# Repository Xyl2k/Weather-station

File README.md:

Weather-station
===============

This is an Arduino powered weather station who run with 5V and who report datas on your own control panel.
You can also launch a cycle from the panel.
An Eagle typon is also available for those who want to print a PCB

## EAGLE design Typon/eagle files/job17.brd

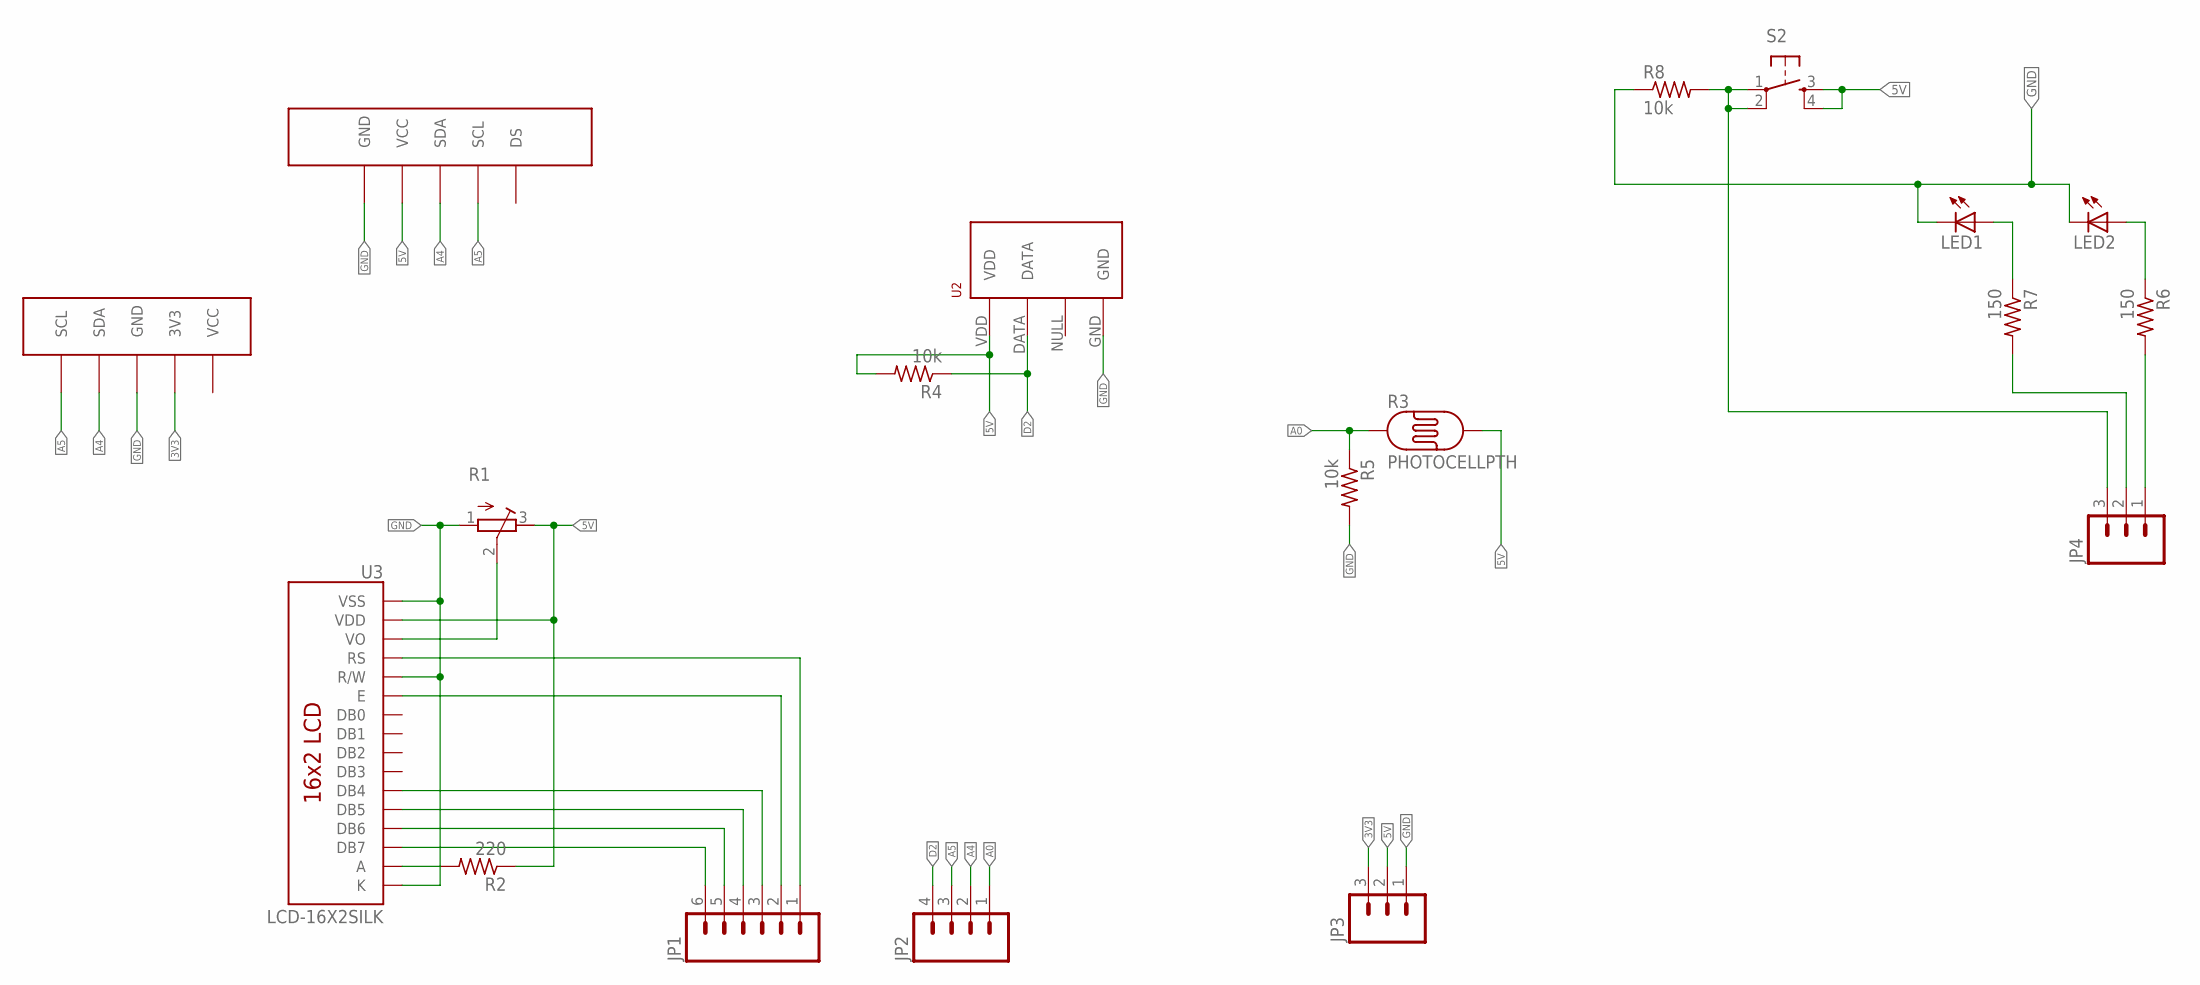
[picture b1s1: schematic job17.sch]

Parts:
JP1: M06SIP; 1X06
JP2: M04PTH; 1X04
JP3, JP4: M03PTH; 1X03
LED1, LED2: LED5MM
R1: R-TRIMM3339P; RTRIM3339P
R2: 220; 0207/10
R3: PHOTOCELLPTH; PHOTOCELL
R4, R5, R8: 10k; 0207/10
R6, R7: 150; 0207/10
RTC1: TINY_RTC
S1: BMP085
S2: TAC_SWITCHPTH; TACTILE-PTH
U2: RHT03_DHT-22_AM2302RA; RHT03_DHT-22/RA
U3: LCD-16X2SILK; LCD-16X2

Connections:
3V3: JP3.3, S1.3V3
5V: JP3.2, R1.3 (E), R2.1, R3.2, R4.2, RTC1.VCC, S2.3, S2.4, U2.VDD, U3.2 (VDD)
A0: JP2.1, R3.1, R5.1
A4: JP2.2, RTC1.SDA, S1.SDA
A5: JP2.3, RTC1.SCL, S1.SCL
D2: JP2.4, R4.1, U2.DATA
D22: JP4.1, R6.2
D24: JP4.2, R7.2
D26: JP4.3, R8.2, S2.1, S2.2
GND: JP3.1, LED1.K (C), LED2.K (C), R1.1 (A), R5.2, R8.1, RTC1.GND, S1.GND, U2.GND, U3.1 (VSS), U3.5 (R/W), U3.16 (K)
unnamed: JP1.6, U3.14 (DB7)
unnamed: JP1.5, U3.13 (DB6)
unnamed: R1.2 (S), U3.3 (VO)
unnamed: R2.2, U3.15 (A)
unnamed: JP1.4, U3.12 (DB5)
unnamed: JP1.3, U3.11 (DB4)
unnamed: JP1.2, U3.6 (E)
unnamed: JP1.1, U3.4 (RS)
unnamed: LED1.A, R7.1
unnamed: LED2.A, R6.1

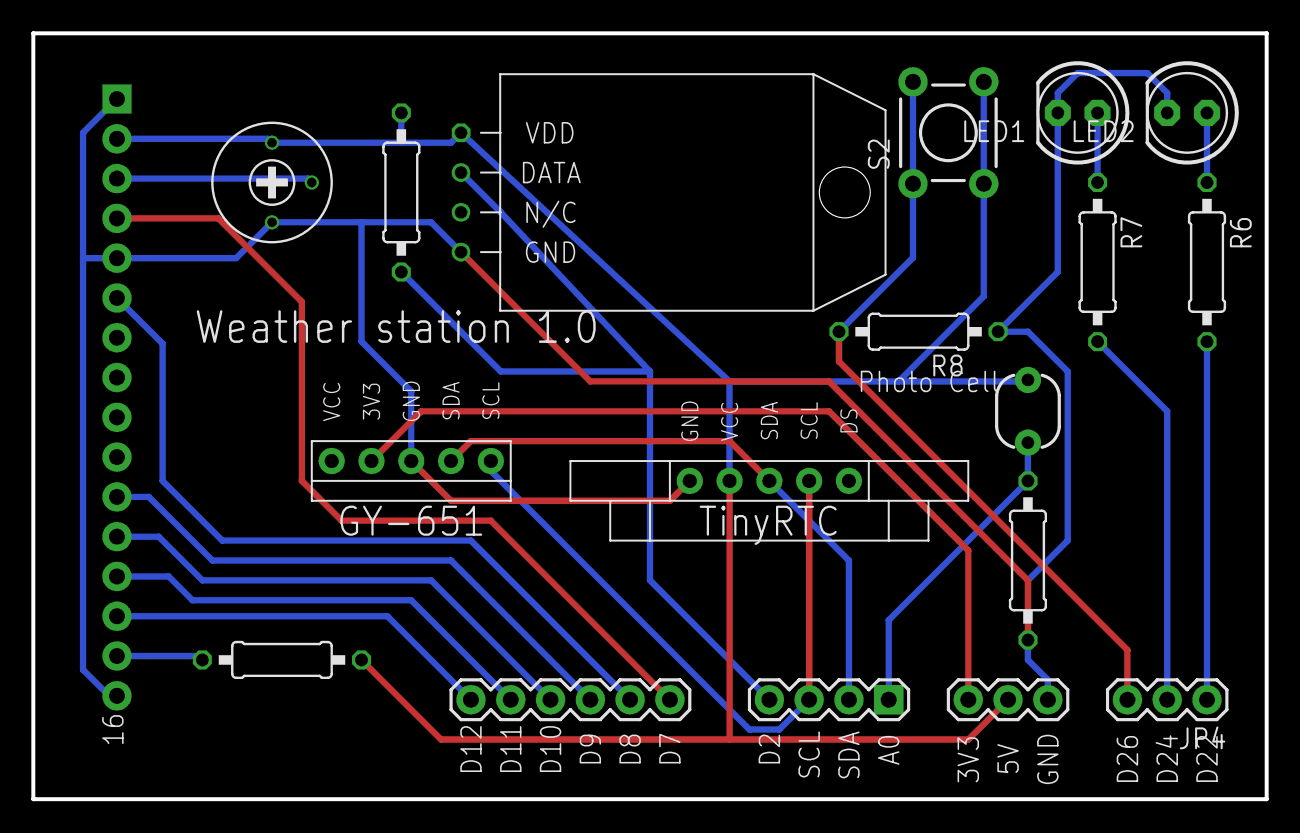
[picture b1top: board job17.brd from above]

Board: 2 copper layers, 78.7 x 48.9 mm, 19 parts (0 on the bottom side), 20 nets.

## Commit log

2014-08-29 :boom::camel: Added .gitattributes & .gitignore files
2014-08-29 Added stuff
    Added stuff

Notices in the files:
parts and their libraries:
SparkFun-Sensors: Licensing: CC v3.0 Share-Alike You are welcome to use this library for commercial purposes.
